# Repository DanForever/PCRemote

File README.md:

# Remote control ATX power switch

An alternative, Internet of things (IoT) approach to Wake-on-Lan (WoL).

This is a device that you plug into a free USB2 motherboard header in order to draw power (assuming that your motherboard continues to provides power to the USB headers when turned off), and sits inbetween the motherboard front panel IO header and your case.
It will connect to your wifi, and you can access it using your web browser, and press a button to remote turn your PC on or off.

This was created for people for whom WoL isn't an option, but need to be able to check and control the power status of their PC remotely (such as people that work from home using some form of remote desktop software).

WoL works by broadcasting a special packet containing the mac address of the PC you want to turn on. Until your PC starts responding to normal requests, you don't actually know if the WoL packet worked or not, and you have no way of checking if your PC is functioning.
This device on the other hand, can tell you at a glance if your PC is on or off. There's less ambiguity involved.

## Prototype
This is the first prototype, made entirely using THT parts

## Prerequisites
### [ESPTool](https://github.com/espressif/esptool "Esptool")
This is for flashing the firmware and the filesystem to the microcontroller
### [Arduino-CLI](https://github.com/arduino/arduino-cli)
To compile the firmware
Also requires these libraries:
* [ESP8266WiFi](https://github.com/esp8266/Arduino)
 * [ESP8266WebServer](https://github.com/esp8266/Arduino/tree/master/libraries/ESP8266WebServer)
  * [EEPROM](https://github.com/esp8266/Arduino/tree/master/libraries/EEPROM)
  * [LittleFS](https://github.com/esp8266/Arduino/tree/master/libraries/LittleFS)
* [ArduinoJson](https://arduinojson.org/)
* [StreamUtils](https://github.com/bblanchon/ArduinoStreamUtils)
* [DF-Print](https://github.com/DanForever/DF-Print)

### [mklittlefs](https://github.com/earlephilhower/mklittlefs)
This is for creating the filesystem binary

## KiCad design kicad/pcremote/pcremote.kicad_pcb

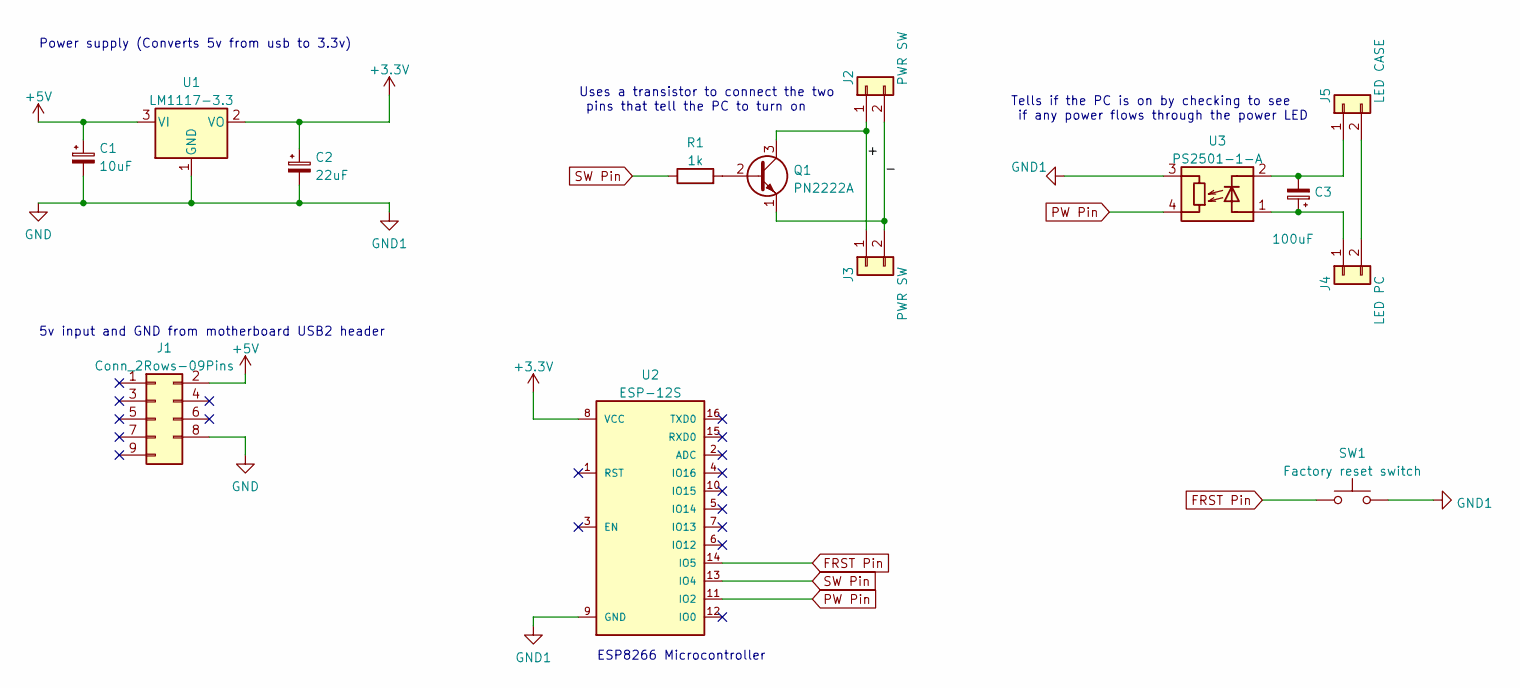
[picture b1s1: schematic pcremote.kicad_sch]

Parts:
C1: 10uF; CP_Radial_D5.0mm_P2.50mm
C2: 22uF; CP_Radial_D5.0mm_P2.50mm
C3: 100uF; CP_Radial_D5.0mm_P2.50mm
J1: Conn_2Rows-09Pins; PinSocket_2x05_P2.54mm_Horizontal
J2, J3: PWR SW; PinHeader_1x02_P2.54mm_Horizontal
J4: LED PC; PinHeader_1x02_P2.54mm_Horizontal
J5: LED CASE; PinHeader_1x02_P2.54mm_Horizontal
Q1: PN2222A; TO-92_Inline
R1: 1k; R_Axial_DIN0207_L6.3mm_D2.5mm_P10.16mm_Horizontal
SW1: Factory reset switch; SW_PUSH_6mm
U1: LM1117-3.3; TO-220-3_Vertical
U2: ESP-12S
U3: PS2501-1-A; DIP-4_W7.62mm

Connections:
+3.3V: C2.1, U1.2 (VO), U2.8 (VCC)
+5V: C1.1, J1.2, U1.3 (VI)
/+: J2.1, J3.1, Q1.3 (C)
/-: J2.2, J3.2, Q1.1 (E)
FRST Pin: SW1.1, U2.14 (IO5)
GND: C1.2, C2.2, J1.8, SW1.2, U1.1 (GND), U2.9 (GND), U3.3 (R)
unnamed: C3.1, J4.1, U3.1 (A)
unnamed: C3.2, J5.1, U3.2 (K)
unnamed: J4.2, J5.2
unnamed: Q1.2 (B), R1.2
PW Pin: U2.11 (IO2), U3.4 (R)
SW Pin: R1.1, U2.13 (IO4)

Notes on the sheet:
5v input and GND from motherboard USB2 header
ESP8266 Microcontroller
Uses a transistor to connect the two pins that tell the PC to turn on
Power supply (Converts 5v from usb to 3.3v)
Tells if the PC is on by checking to see if any power flows through the power LED

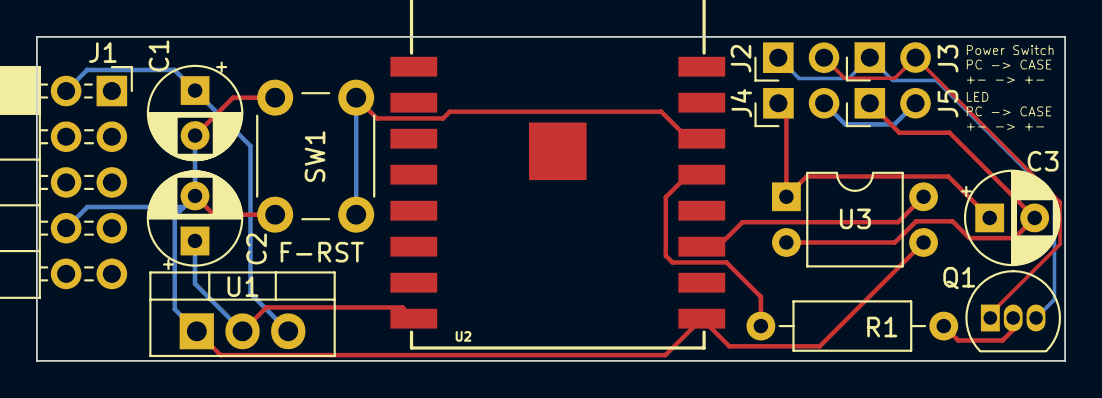
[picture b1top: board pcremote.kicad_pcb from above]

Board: 2 copper layers, 57.1 x 18.0 mm, 14 parts (0 on the bottom side), 12 nets.

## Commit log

2022-08-05 Initial checkin
    Contains the first working prototype of the remote control atx power switch
2022-08-05 Added bare basic information to readme
2022-08-05 Minor formatting change
2022-08-10 Create PCRemoteControl.ino
    The root .ino missing from the original checkin
2022-08-11 Support for credentials
    Digest Authentication, supports both SHA-256 as well as basic MD5 (can switch to SHA256 when chrome finally supports it)
2022-08-11 Updated the readme with an introduction
2022-08-11 Fixed the path to the image (hopefully)
2022-08-12 Replaced Serial.print with a more user friendly set of debug print functions
2022-08-12 Added missing license header
2022-08-12 Fixed log line
2022-08-15 Refactored to use DF-Print
    Removed DebugPrint.h, as all the functionality is now published as a separate library
